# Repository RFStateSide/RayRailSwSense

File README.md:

# RayRailSwSense

RayRailSwSense is RF StateSide LLC's high-side DC rail switch with current and
switched-output voltage sensing for amplifier and instrumentation development.

**Public Engineering Reference — AS-IS.** Editable KiCad sources, a population
BOM and manufacturing files support study, independent construction,
modification and continued development.

## Hardware and History

PCBWay manufactured the redesigned BTH board. We hand-populated it using a
reflow oven and successfully tested it with RayPowerMeter and RaySspaController.
The tested assembly used BTH500301LUAAUMA1, R4 = 2 kΩ, a Murata BLM31PG121SN1L
ferrite bead and a 25 A, 32 VDC automotive-type fuse. The fuse rating is not
evidence of a measured 25 A continuous test.

BTH500151LUAAUMA1 is an alternative device selection, not a separately verified
assembly or a higher-rated board variant. See [assembly and history](docs/assembly-and-history.md).

The supplied P2-prep-01 files reconcile the tested population and source
metadata while retaining the original copper, drilling, placement and routing.
Revised labeling and regenerated outputs distinguish this package from the
original fabrication submission. This prepared revision has not itself been
fabricated or physically tested.

## Operating Limits

The installed 178.6165.0002 fuse holder has a 32 VDC maximum, 30 A maximum
current and a manufacturer's 22.5 A continuous component figure. These are
component limits, not a complete-board operating specification. No guaranteed
continuous board current is established. Do not operate above the installed
holder's limits. See [known limitations](docs/known-limitations.md).

The sense connector is not directly interchangeable with the saved
RaySspaController connector revisions. Pin 1 carries raw switched rail voltage.
Use the [integration guide](docs/integration.md), not a straight-through cable
assumption. Current-sense fault output is not guaranteed to remain within 3.3 V.

## Opening and Building

Open [the KiCad 9 project](hardware/RayRailSwSense.kicad_pro). Required symbols
and footprints are included in project-local libraries; optional 3D models are
omitted. [View schematic](docs/images/RayRailSwSense.svg) ·
[View PCB front](docs/images/pcb-front.svg).

Use the [BOM](bom/RayRailSwSense.csv) and [manufacturing instructions](manufacturing/README.md)
together. FB1's owner-confirmed 1206 component is represented on the retained
0805 lands: this is an explicit historical fit limitation, not a standard
land-pattern recommendation.

## Repository Contents

| Location | Contents |
|---|---|
| hardware/ | Portable editable project and local libraries |
| bom/ | Tested-population procurement reference and assembly notes |
| manufacturing/ | Identified Gerber, drill, placement and BOM package |
| docs/ | Integration, history, limitations, provenance and verification |
| tools/ | Generation and integrity/engineering verification utilities |
| PUBLIC_RELEASE_AUDIT.md | Attributed technical validation record |

Original historical designs, supplier records and fabrication archives are
retained separately. No parent firmware or development-repository history is included.

## Development Tools

KiCad was used for schematic capture and PCB design. Python utilities support
source verification and manufacturing-package integrity checks. Git and GitHub
are the intended version-control and distribution tools.

ChatGPT by OpenAI and OpenAI Codex assisted with engineering review,
documentation, source organization, validation and preparation of the
open-hardware reference. RF StateSide LLC performed the original hardware
design, assembly and historical integration testing.

## License and Credits

Copyright RF StateSide LLC. Original contributions are provided under
**CERN-OHL-P v2.0**, SPDX **CERN-OHL-P-2.0**. The unmodified [LICENSE](LICENSE)
is authoritative; retain [NOTICE](NOTICE) and applicable library notices.
See [licensing](docs/licensing.md) and [provenance](docs/provenance.md).

RF StateSide created the project-specific symbols and custom footprints.
KiCad contributors supplied the stock and upstream-derived definitions.
No certification, guaranteed performance, future development or technical
support is promised.

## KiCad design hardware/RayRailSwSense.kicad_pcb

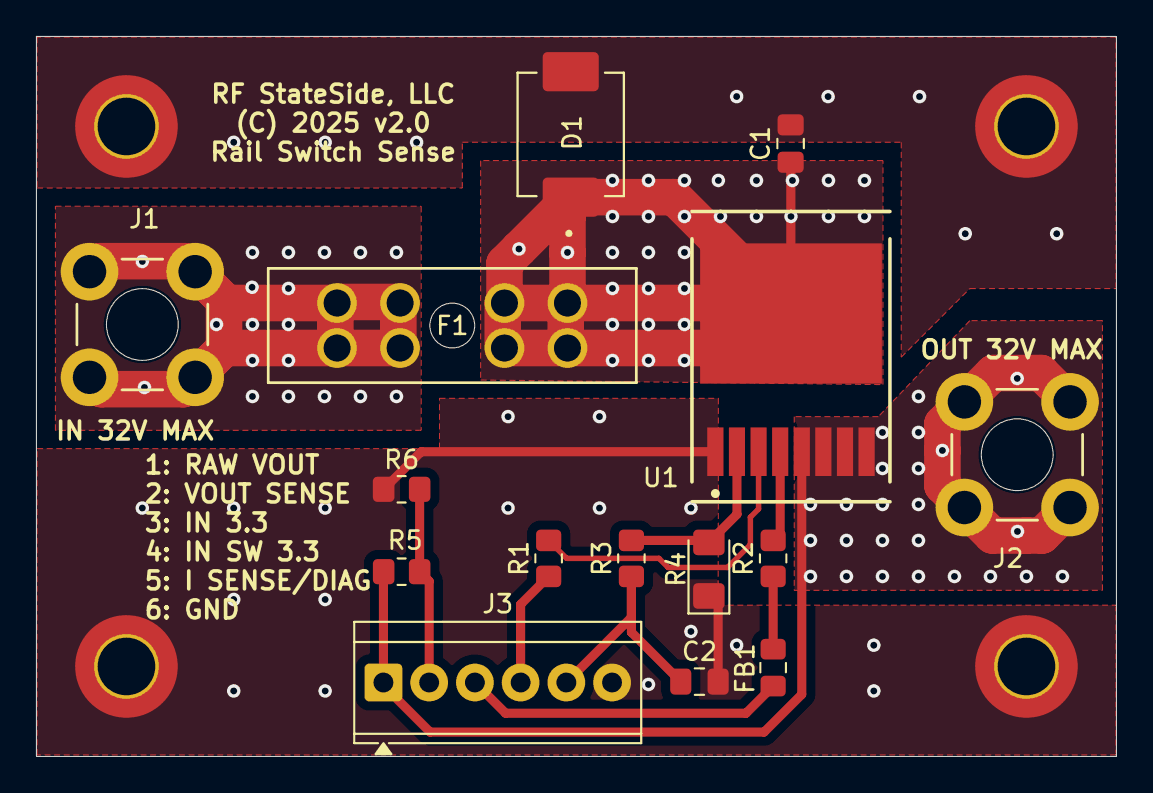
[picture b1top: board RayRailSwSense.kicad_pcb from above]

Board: 2 copper layers, 60.0 x 40.0 mm, 19 parts (0 on the bottom side), 12 nets.

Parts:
C1: .1 µF; Capacitor_SMD_C_0805_2012Metric_Pad1.18x1.45mm_HandSolder
C2: .01 µF; Capacitor_SMD_C_0805_2012Metric_Pad1.18x1.45mm_HandSolder
D1: SMCJ85A; MyFootprints_DIOM7959X262N
F1: 178.6165.0002; MyFootprints_FUSE_178.6165.0002_LTF
FB1: BLM31PG121SN1L; Inductor_SMD_L_0805_2012Metric_Pad1.15x1.40mm_HandSolder
H1, H2, H3, H4: MountingHole_3.2mm_M3_ISO7380_Pad_TopBottom_Gnd; MyFootprints_MountingHole_3.2mm_M3_ISO7380_Pad_TopBottom_Gnd
J1, J2: 74650074R; MyFootprints_CONN_74650074R_WRE
J3: Screw_Terminal_01x06; TerminalBlock_TE-Connectivity_TerminalBlock_TE_282834-6_1x0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
R1, R2, R3, R6: 4.7K; Resistor_SMD_R_0805_2012Metric_Pad1.20x1.40mm_HandSolder
R4: 2k; LED_SMD_LED_1206_3216Metric_Pad1.42x1.75mm_HandSolder
R5: 82K; Resistor_SMD_R_0805_2012Metric_Pad1.20x1.40mm_HandSolder
U1: BTH50030-1LUA; MyFootprints_IFX-PG-HSOF-5-6-7-8

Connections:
+3.3V: FB1.1, R2.1
+VDC: J2.1, J2.2, J2.3, J2.4, J3.1, R5.2, U1.5 (OUT1), U1.6 (OUT2), U1.7 (OUT3), U1.8 (OUT4)
GND: C1.2, C2.2, D1.A, H1.1, H2.1, H3.1, H4.1, J3.6, R4.1, R6.1, U1.1 (GND)
unnamed: F1.1, F1.2, F1.3, F1.4, J1.1, J1.2, J1.3, J1.4
unnamed: J3.2, R5.1, R6.2
unnamed: FB1.2, J3.3
unnamed: J3.4, R1.1
unnamed: C2.1, J3.5, R3.1
unnamed: R2.2, U1.4 (DEN)
unnamed: R1.2, U1.3 (IN)
unnamed: R3.2, R4.2, U1.2 (IS)
unnamed: C1.1, D1.C, F1.5, F1.6, F1.7, F1.8, U1.9 (VS)

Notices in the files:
hardware/RayRailSwSense.kicad_pcb:
(C) 2025 v2.0
